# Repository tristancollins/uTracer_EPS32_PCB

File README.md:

# uTracer_EPS32_PCB
A PCB to contain an ESP32 to interface with a uTracer

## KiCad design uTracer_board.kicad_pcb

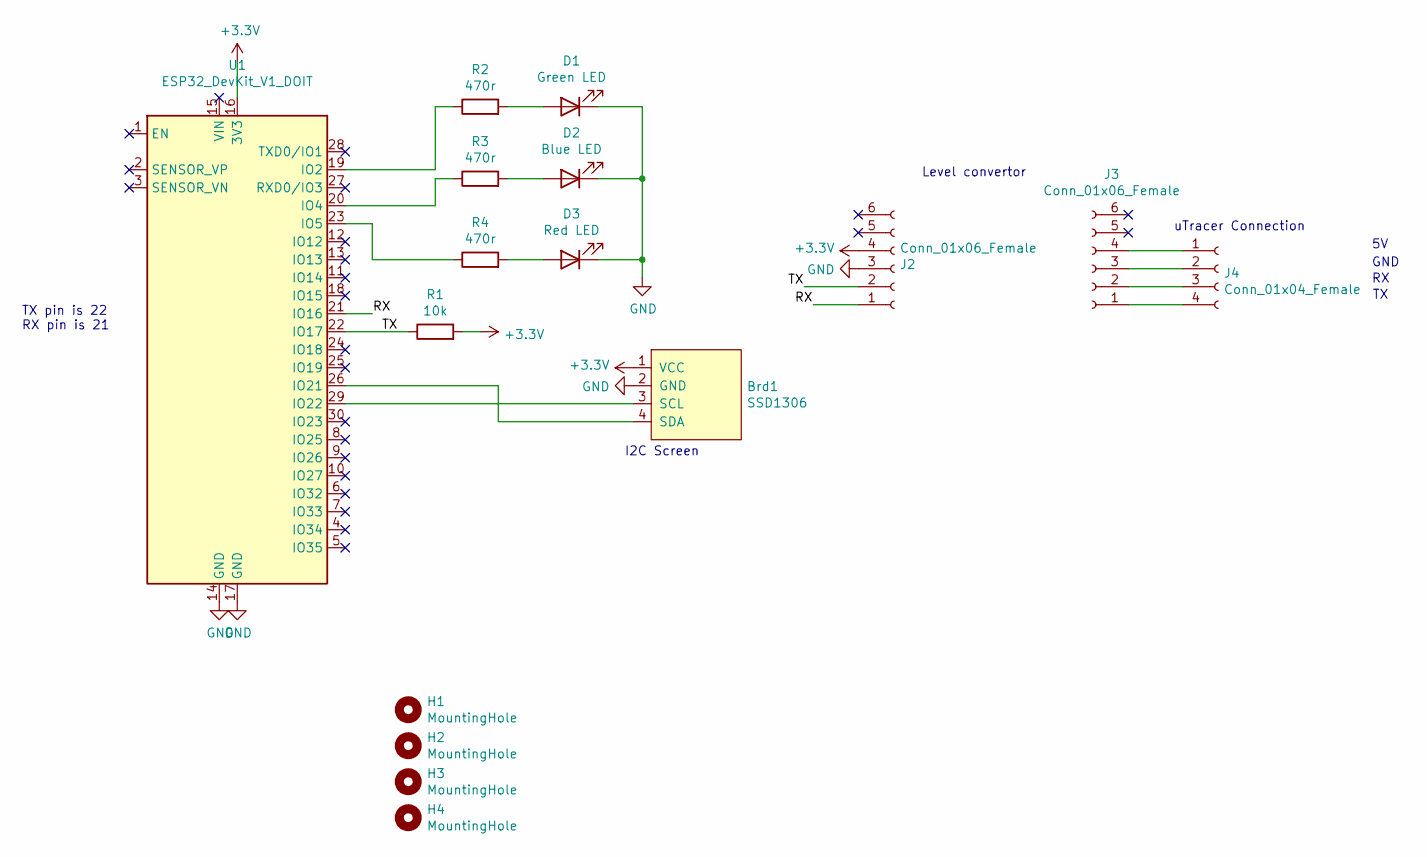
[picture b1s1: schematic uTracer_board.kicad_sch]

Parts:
Brd1: SSD1306; 128x64OLED
D1: Green LED; LED_D3.0mm
D2: Blue LED; LED_D3.0mm
D3: Red LED; LED_D3.0mm
H1, H2, H3, H4: MountingHole; MountingHole_3.2mm_M3
J2, J3: Conn_01x06_Female; PinSocket_1x06_P2.54mm_Vertical
J4: Conn_01x04_Female; PinSocket_1x04_P2.54mm_Vertical
R1: 10k; R_Axial_DIN0207_L6.3mm_D2.5mm_P10.16mm_Horizontal
R2, R3, R4: 470r; R_Axial_DIN0207_L6.3mm_D2.5mm_P10.16mm_Horizontal
U1: ESP32_DevKit_V1_DOIT; esp32_devkit_v1_doit

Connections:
+3V3: Brd1.1 (VCC), J2.4, R1.2, U1.16 (3V3)
/RX: J2.1, U1.21 (IO16)
/TX: J2.2, R1.1, U1.22 (IO17)
GND: Brd1.2 (GND), D1.1 (K), D2.1 (K), D3.1 (K), J2.3, U1.14 (GND), U1.17 (GND)
unnamed: Brd1.3 (SCL), U1.29 (IO22)
unnamed: Brd1.4 (SDA), U1.26 (IO21)
unnamed: D1.2 (A), R2.2
unnamed: D2.2 (A), R3.2
unnamed: D3.2 (A), R4.2
unnamed: J3.1, J4.4
unnamed: J3.2, J4.3
unnamed: J3.3, J4.2
unnamed: J3.4, J4.1
unnamed: R2.1, U1.19 (IO2)
unnamed: R3.1, U1.20 (IO4)
unnamed: R4.1, U1.23 (IO5)

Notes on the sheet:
uTracer Connection
TX pin is 22 RX pin is 21
Level convertor
GND
I2C Screen

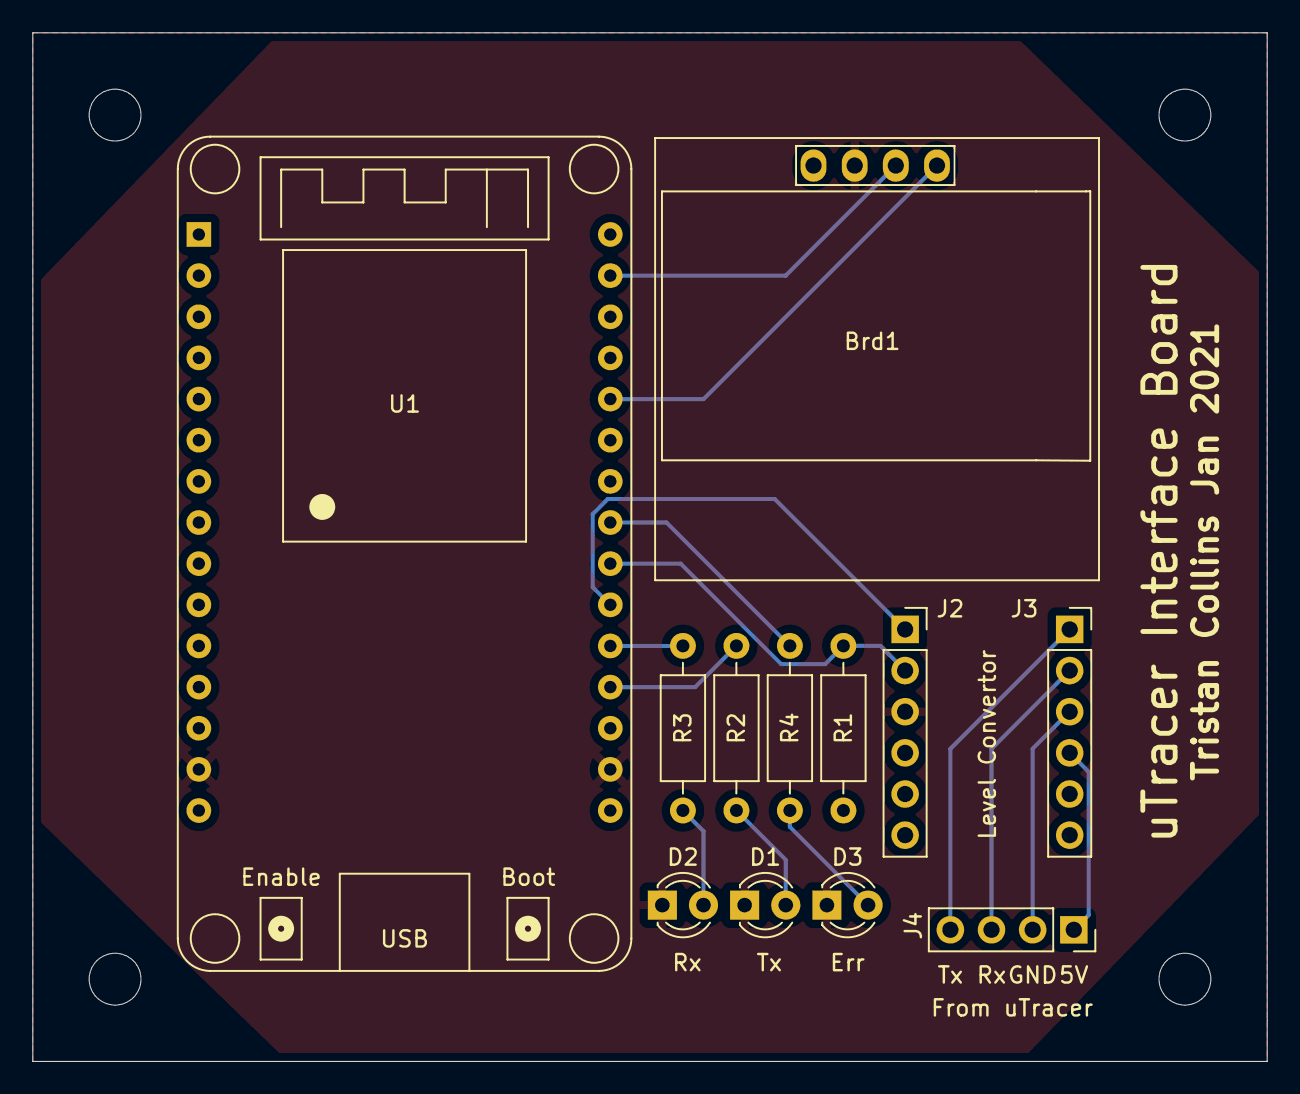
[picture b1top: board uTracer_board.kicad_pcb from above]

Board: 2 copper layers, 76.2 x 63.5 mm, 16 parts (0 on the bottom side), 16 nets.

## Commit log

2021-12-20 updated layout and mechanics
2021-12-22 update silkscreen and adjust schemo
2021-12-31 switching to KiCADv6
2022-01-02 minor tweaks
2022-01-10 tweaks
2022-01-15 adding gerbers
